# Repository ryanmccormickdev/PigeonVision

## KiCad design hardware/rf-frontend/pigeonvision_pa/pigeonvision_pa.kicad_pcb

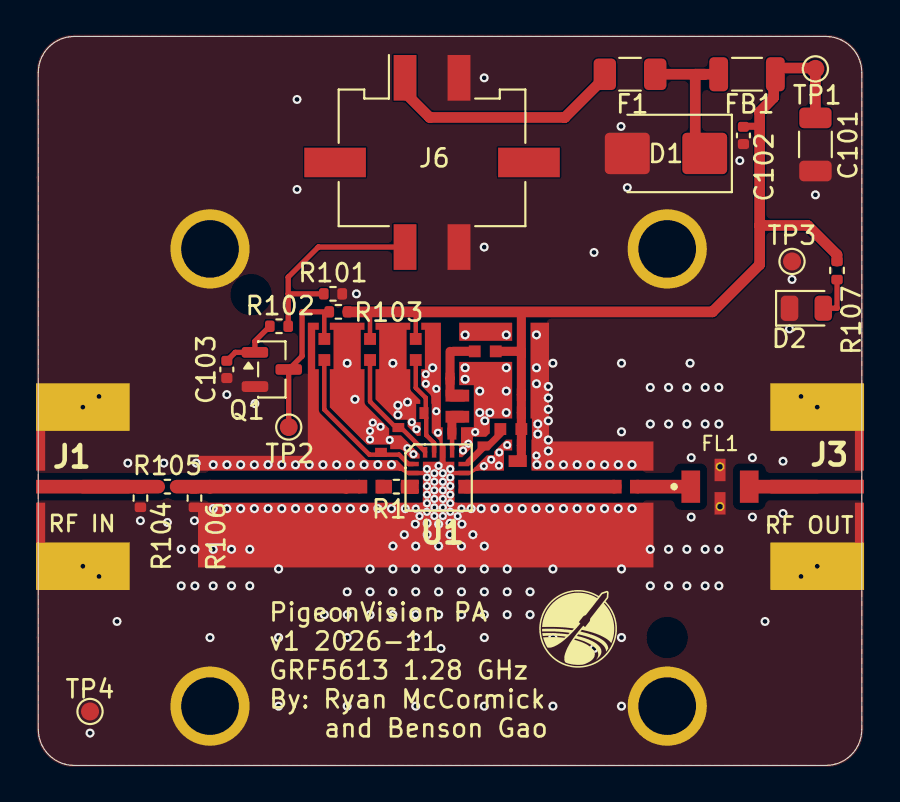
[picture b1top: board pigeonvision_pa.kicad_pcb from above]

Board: 4 copper layers, 45.8 x 40.5 mm, 53 parts (0 on the bottom side), 21 nets.

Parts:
C101: 22µF; C_1206_3216Metric
C102: 0.1µF; C_0402_1005Metric
C103: 1nF; C_0402_1005Metric
D1: SMBJ5.0A; D_SMB
D2: GREEN; LED_0805_2012Metric
F1: 2A; Fuse_1206_3216Metric
FB1: FerriteBead; L_1206_3216Metric
FL1: LFCN-1400+; MiniCircuits_FV1206_LFCN
H1: Heatsink; Heatsink_wFid
J1, J3: SMA; SMA Round_Pin_RevC
J6: Micro-Fit 3.0 4p; Molex_Micro-Fit_3.0_43045-0418_2x02-1MP_P3.00mm_Vertical
M1: 2.4nH; 0402_20x26x22
M2: 6.2pF; 0402_20x30x18
M4, M11, M15, M16: 0Ω; 0402_26x26x20
M5: 15kΩ; 0402_26x26x20
M6, M13, M14, M19: DNP; 0402_20x26x16
M7, M8, M10: 0.1µF; 0402_20x26x16
M9: 5.62kΩ; 0402_26x26x20
M12: DNP; 0402_26x26x20
M17: 10µF; 0402_20x26x16
M18: 33pF; 0402_20x26x16
M20: 4.3pF; 0402_20x26x22
M21, M24, M25, M26: DNP; 0402_20x26x22
M22: 23nH; 0603_26x40x30
M23: 2.2pF; 0402_20x26x22
M27: 3.6pF; 0402_20x26x22
M28: 22pF; 0402_20x30x18
Q1: 2N7002; SOT-23
R1: 2Ω; R_0402_1005Metric
R101: 10kΩ; R_0402_1005Metric
R102: 1kΩ; R_0402_1005Metric
R103: 18kΩ; R_0402_1005Metric
R104, R106: 220Ω; R_0402_1005Metric
R105: 24Ω; R_0402_1005Metric
R107: 1.5kΩ; R_0402_1005Metric
TP1: 5V_PA; TestPoint_Pad_D1.0mm
TP2: PA_SHDN; TestPoint_Pad_D1.0mm
TP3, TP4: GND; TestPoint_Pad_D1.0mm
U1: GRF5613; QFN16_3x3mm_RevG

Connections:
5V_PA: C101.2, C102.2, FB1.2, M5.2, M9.2, M15.1, M16.1, M17.2, M18.2, M19.2, M22.2, R103.1, R107.1, TP1.1
/PA Enable/PA_EN: J6.3, R101.1, R102.1
/PA Enable/PA_SHDN: M4.2, Q1.3, R103.2, TP2.1
/Power Entry/5V_RF: F1.1, J6.1
/RF Chain/RF_IN_SMA: J1.1, R104.1, R105.1
/RF Chain/RF_LPF_IN: FL1.1, M28.1
/RF Chain/RF_OUT_SMA: FL1.3, J3.1
/RF Chain/RF_PA_IN: M1.2, M2.2, R105.2, R106.1
/RF Chain/RF_PA_OUT: M20.2, M21.2, M22.1, M23.2, M24.2, M25.2, M26.2, M27.2, M28.2, U1.9, U1.10
GND: C101.1, C102.1, C103.1, D1.2, D2.1, FL1.2, FL1.4, H1.1 (1_1), J1.2, J3.2, J6.2, J6.4, M1.1, M6.1, M7.1, M8.1, M10.1, M13.1, M14.1, M17.1, M18.1, M19.1, M20.1, M21.1, M23.1, M24.1, M25.1, M26.1, M27.1, Q1.2, R101.2, R104.2, R106.2, TP3.1, TP4.1, U1.2, U1.5, U1.6, U1.7, U1.8, U1.11, U1.14, U1.17
unnamed: D1.1, F1.2, FB1.1
unnamed: D2.2, R107.2
unnamed: M2.1, R1.1
unnamed: M4.1, M6.2, U1.1
unnamed: M5.1, M7.2, U1.16
unnamed: M8.2, M9.1, U1.15
unnamed: M10.2, M11.2, M12.2, M15.2
unnamed: M11.1, M12.1, M13.2, U1.13
unnamed: M14.2, M16.2, U1.12
unnamed: C103.2, Q1.1, R102.2
unnamed: R1.2, U1.3, U1.4
